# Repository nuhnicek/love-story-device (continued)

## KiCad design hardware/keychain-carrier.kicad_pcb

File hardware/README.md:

# Hardware — GSM touch keychain

Two boards per keychain:

1. **Carrier** (this folder): a 2-layer, **0.8 mm** board with the **same 25.2 × 23.0 mm
   outline as the red SIM800L mini module**. The module sits on top and is soldered
   straight through its own 12 holes. All electronics are on the **bottom** side, facing
   the LiPo cell. The separate TP4056 board is gone: USB-C and a TP4054 charger chip are
   on the carrier.
2. **Heart LED board**: hand-built on a **universal board** (11 × 9 holes) with **10 × 3 mm
   LEDs** in a heart, one resistor each, and the coin motor in the middle. The LED domes
   stick out through holes in the case lid. Wired to the carrier's `HEART +/-` pads. See
   [Heart LED board](#heart-led-board).

Cost: see [COST.md](COST.md). ≈ 1 450–2 900 Kč for the self-assembled pair incl. 1NCE SIMs
for 10 years. Firmware: [`../firmware`](../firmware). Relay server: [`../server`](../server).

| File | What |
|---|---|
| `keychain-carrier.kicad_sch` | **Schematic** (KiCad 10). PDF/SVG: `fab/schematic.pdf`, `fab/schematic.svg` |
| `keychain-carrier.kicad_pcb` / `.kicad_pro` / `.kicad_dru` | KiCad 10 board, project, custom DRC rule |
| `keychain.kicad_sym`, `keychain.pretty/`, `sym-lib-table`, `fp-lib-table` | Project library: SIM800L symbol + footprint, VBAT power symbol, wire pads |
| `netlist.txt` | Netlist extracted from the board copper |
| `BOM.md` | Full parts list (carrier + perfboard heart + off-board) |
| `COST.md` | Manufacturing and running-cost estimate |
| `fab/keychain-carrier-gerbers.zip` | Gerbers + Excellon drill, ready to upload |
| `fab/keychain-carrier-bom-jlcpcb.csv`, `fab/keychain-carrier-pos-bottom.csv` | JLCPCB assembly files (bottom side) |
| `fab/assembly-bottom.pdf` | Assembly drawing with designators (bottom, mirrored) |
| `fab/keychain-carrier.step` | 3D model for the enclosure design |
| `scripts/` | Generator: `make_all.sh <freerouting.jar>` rebuilds everything |

Checks (all run by `make_all.sh`):
- **ERC**: 0 violations
- **DRC**: 0 errors, 0 unconnected (one cosmetic silk note)
- **Schematic ↔ PCB parity**: 0 issues. Every footprint is linked to its symbol, and the
  pad nets and fields come from the schematic netlist.

## Pin map (ATtiny85, RESET kept for ISP)

| ATtiny85 pin | Port | Net | Goes to |
|---|---|---|---|
| 1 | PB5 / RESET | RESET | 10 k pull-up to VBAT, ISP pad TP1 |
| 2 | PB3 | RST_DRV | 1 kΩ → SIM800L RST (pin 3). Open-drain hard reset of a hung modem; never driven high |
| 3 | PB4 | DRV | 100 Ω → AO3400A gate (100 k pull-down). Motor **and** heart LEDs |
| 4 | GND | GND | |
| 5 | PB0 / MOSI | MCU_RX | 1 k ← SIM800L TXD (SoftwareSerial RX). ISP TP2 |
| 6 | PB1 / MISO | MCU_TX | 47 k / 100 k divider → SIM800L RXD (≈2.86 V at 4.2 V). ISP TP3 |
| 7 | PB2 / SCK | BTN | Side button to GND (internal pull-up), PCINT2. ISP TP4 |
| 8 | VCC | VBAT | 100 nF |

Five I/O pins can't cover TX, RX, RING, button, motor, LEDs and DTR separately. So:
- **Heart LEDs and motor share PB4.** The heart board hangs in parallel with the motor on
  the MOSFET drain (pads HT1/HT2), so the heart glows exactly with the vibration. Q1 is an
  **AO3400A** (~50 mΩ) instead of the 2N7002 (2–5 Ω). With motor + 14 LEDs (~150 mA) a
  2N7002 would drop 0.3–0.7 V and visibly dim the pink LEDs. Same SOT-23 footprint and pinout.
- **DTR and RING are not used** (1NCE data design). The modem sleeps by itself
  (`AT+CSCLK=2`). Incoming TCP data is held in the modem (`AT+CIPRXGET=1`), and its URC on
  the UART line wakes the ATtiny85. That frees PB3 to hard-reset the modem.
- **SoftwareSerial owns the only PCINT vector** on the ATtiny85. The button shares it
  (`PCMSK |= _BV(PCINT2)`); SoftwareSerial's ISR ignores changes on pins other than its RX.
- **Charger: TP4054** (pin-compatible with the MCP73831; 4.7 kΩ on PROG = 213 mA). It's a
  standalone linear Li-ion charger with thermal regulation, the same circuit class as the
  TP4056, at about a tenth of the MCP73831's price. A transistor-only charger wouldn't be
  cheaper and would be much less safe.
- Firmware: `../firmware`. Relay server: `../server`.

## Schematic (ASCII quick view; the real one is `keychain-carrier.kicad_sch`)

```
 USB-C (power only)                TP4054 (U2)                  LiPo 3.7 V
 VBUS ──┬──────────────────────── 4 VDD     VBAT 3 ──┬───────────── BT1 (+)
        C3 4.7u                     5 PROG─R10 4k7─GND │            BT2 (-) ── GND
 CC1 ── R8 5k1 ── GND               1 CHRG (n.c.)    C4 4.7u
 CC2 ── R9 5k1 ── GND               2 VSS ── GND       │
                                                       │ VBAT
        ┌──────────────────────────────────────────────┼───────────────────┐
        │                                              │                   │
  SIM800L M1 (top side)              C2 470u tant ═╪═ C5 10u       ATtiny85 U1
   2 VCC ──────────────────────────────────────────────┤             8 VCC ──┤ C1 100n
   6 GND ── GND                                         R6 10k ─── 1 RESET ── TP1
   5 TXD ── R1 1k ──────────────────────────────────────────────── 5 PB0 ── TP2
   4 RXD ──┬── R2 47k ──────────────────────────────────────────── 6 PB1 ── TP3
           R3 100k ── GND                                          7 PB2 ── TP4 ── SW1 ── GND
   3 RST ── R7 1k ──────────────────────────────────────────────── 2 PB3 (open drain)
   1 NET, 7–12 (SPK/MIC/DTR/RING): not connected                   3 PB4 ── R4 100R ──┐
                                                                    4 GND             │
  VBAT ─┬─ MT1 (motor +)    VBAT ─ HT1 ═ heart board ═ HT2 ─┐             R5 100k ─┤ G
        │   [0820 motor]                                     │                GND   Q1 AO3400A
        D1 (K)─┘ MT2 (motor −) ──────────────────────────────┴───────────────── D   S ── GND
```

## Silkscreen labels

Every connection point is labelled (0.8 mm text, about the smallest that prints legibly):

- **Bottom:** `BAT` `+`/`-` (battery), `MOT` (motor pads, polarity doesn't matter for a
  coin motor), `HEART` `+`/`-` (heart board wires), and `ISP` with `RST`, `MOSI`, `MISO`,
  `SCK`, `VCC`, `GND` next to each programming pad.
- **Top:** the name of every SIM800L hole (`NET VCC RST RXD TXD GND` / `RING DTR MIC± SPK±`)
  so the module can't go on the wrong way round, plus `TOUCH-GSM v1 / SIM800L SIDE`.

Part references (R1, U1…) are only on the assembly drawing (`fab/assembly-bottom.pdf`);
there's no room for them on the copper side.

## Heart LED board

- **Board:** a universal board (2.54 mm, single-sided pads) cut to **11 × 9 holes =
  27.9 × 22.9 mm**.
- **LEDs:** 10 × 3 mm LEDs stand in a heart, each with its two legs in vertically adjacent
  holes.
- **Resistors:** one 1/8 W resistor per LED, lying flat next to its LED: 470 Ω for
  pink/white/blue LEDs (Vf ≈ 3 V), or 1 kΩ for red. That's ~1.5–3 mA per LED, ≤ 30 mA total.
  Use LEDs from one bag so they match.
- **Motor:** the 0820 coin motor sticks onto the free middle of the heart, on the component
  side.
- **Wiring** (underside, insulated thin wire): bridge each LED's anode to the resistor end
  next to it. One wire joins all the far resistor ends (`+`, to the carrier's `HEART +` =
  HT1). Another joins all the LED cathodes (`-`, to `HEART -` = HT2).
- **Hole-by-hole list:** `enclosure/out/heart_perfboard.txt`. The layout comes from
  `enclosure/heart_perfboard.py`, which also writes the LED and post positions the case lid
  uses, so the lid holes always match the drawing.
- **LED height:** the LEDs must sit **flat on the board** (flange down). The lid is
  designed for LEDs 5.3 mm tall from flange to dome top. If yours differ, set `led_h` in
  `enclosure/keychain_case.scad` and rebuild.

## Battery connection

There's no plug-in connector. The LiPo leads solder straight onto two 1.5 × 1.5 mm pads
(2 mm apart) in the **middle of the bottom side**, just above the USB-C and below the
ATtiny85. Looking at the bottom with the USB-C toward you, **BT1 "+" (red) is on the right
and BT2 "−" (black) is on the left**. Both are marked on the silkscreen. There is **no
reverse-polarity protection**, so check twice before soldering. A JST-SH 1.0 mm 2-pin
socket (~2.9 mm tall) could replace the pads if you want a pluggable battery.

## Assembly order (important)

1. **Flash the ATtiny85 before the SIM800L goes on.** The ISP pads (TP1–TP6, bottom-left)
   share the VBAT rail with the SIM800L, which has an **absolute maximum of 4.4 V**. A 5 V
   Arduino-as-ISP powering VCC (or driving 5 V signals into a 4 V target) will hurt the
   module. Use either (a) program the bare carrier, or (b) a 3.3 V programmer with the
   battery connected and the programmer's VCC wire left off.
2. Solder all bottom-side SMD parts (or order JLCPCB assembly with the CSV/POS files).
   The KiCad footprint for the USB-C is GCT USB4125; cheap "TYPE-C 6P" clones share
   the land, but check the drawing.
3. Insert the micro-SIM into the module, then place the module on the carrier top. The
   SIM holder rests on the solder-masked carrier, giving ~1.5 mm spacing. Push 12 pins
   (from a header strip, plastic removed) through both boards, solder both sides, and cut
   flush on the bottom.
4. Wire the battery to BT1/BT2 and the motor to MT1/MT2 (≈20 mm leads, the motor sticks
   to the enclosure wall).
5. Wire the heart perfboard: its `+` wire to carrier `HEART +` (HT1) and its `-` wire to
   `HEART -` (HT2), ~25 mm each. It sits on top of the SIM800L (tape in between), LEDs up.

## Things to check before ordering

- **SIM800L hole geometry.** Taken from a community footprint: rows **21.87 mm** apart,
  2.54 mm pitch, right row (RING…SPK−) offset one pitch lower than the left row
  (NET…GND), outline 25.2 × 23 mm. Measure your Hadex M374C with calipers and change
  `ROW_DX` / `RIGHT_ROW_DY` / `BW` / `BH` in `scripts/build_pcb.py` if needed, then rerun
  `make_all.sh`.
- **Tantalum C2.** 4.2 V on a 6.3 V *MnO₂* tantalum breaks the usual 50 % derating, and
  those fail short on inrush (e.g. when the battery is first connected). Use a **polymer**
  tantalum (Kemet T520D477M006…, listed in the BOM) or a 10 V part.
- **Battery must have its own protection PCM.** The carrier has no over-discharge cut-off.
- **2G availability in Czechia.** Czech operators switched off 3G but still run 2G. Check
  that your operator's 2G will stay on for as long as you want the keychains to work.

## Height budget (for the enclosure)

| Layer | mm |
|---|---|
| SIM800L module incl. shield | ~3.0 |
| SIM holder gap (module underside) | ~1.5 |
| Carrier PCB | 0.8 |
| Tallest bottom part (USB-C 3.2 / tantalum 3.1) | 3.2 |
| LiPo | 4.0 |
| Heart perfboard: wiring underneath 1.3 + board 1.6 + space up to the lid 2.6 | ~5.5 |
| **Total inside** | **~18.4** (case 20.8 mm + 1.5 mm LED domes) |

The 11 mm target can't be reached with a Case-D tantalum, a top-mount USB-C and a 4 mm
cell all stacked. To get close: use a 3 mm cell (e.g. 302025, ~150 mAh) and pocket the
battery around the USB-C/tantalum.

## Design flow / editing

`gen_schematic.py` → `.kicad_sch` (source of truth)
→ `build_pcb.py` places footprints, then **imports nets and fields from the schematic
netlist** (and fails if they disagree with its own pin map)
→ `autoroute.py` (Freerouting, retried with varied pass budgets; fails if anything stays
unrouted) → GND pours (carrier) → DRC + parity + ERC → fab outputs.
Shared code: `schlib.py` (schematic writer), `pcblib.py` (pcbnew helpers), `sexpr.py`.

To change the circuit, edit the scripts and rerun `make_all.sh`. Regenerating
overwrites the `.kicad_sch` / `.kicad_pcb`, so if you'd rather edit by hand in KiCad
from now on, stop running the scripts and use KiCad's *Update PCB from Schematic*. The
footprint↔symbol links are already in place.

## Regenerate

```sh
# needs KiCad 10 and Java 25+ for Freerouting 2.5.0
curl -LO https://github.com/freerouting/freerouting/releases/download/v2.5.0/freerouting-2.5.0.jar
# sha256 f6f51bb02245e8e717f9359bd260cc9c5c0b1bc0acc8b7cb2cd5b8ffeb5de3c7
hardware/scripts/make_all.sh ./freerouting-2.5.0.jar
```

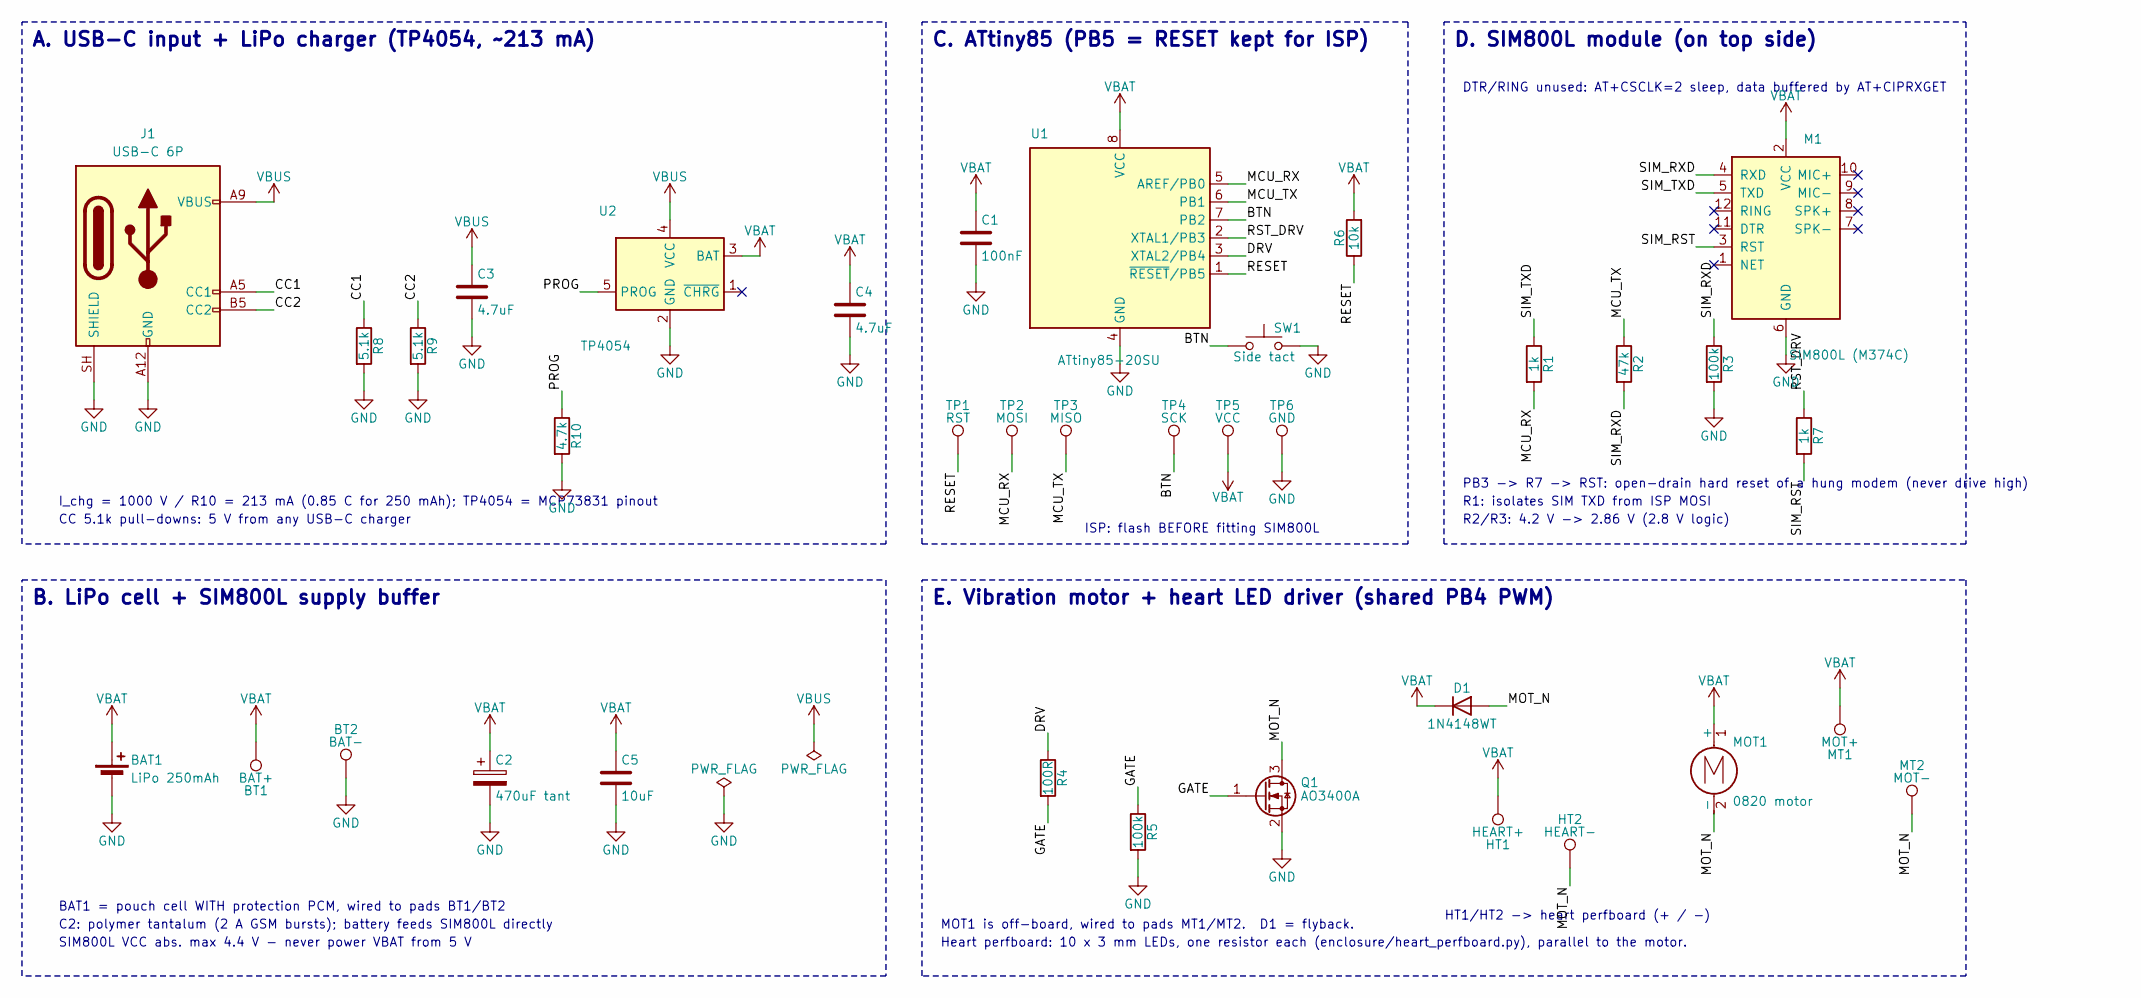
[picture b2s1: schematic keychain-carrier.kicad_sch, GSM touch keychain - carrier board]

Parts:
BAT1: LiPo 250mAh
BT1: BAT+; WirePad_1.5mm
BT2: BAT-; WirePad_1.5mm
C1: 100nF; C_0402_1005Metric
C2: 470uF tant; CP_EIA-7343-31_Kemet-D
C3, C4: 4.7uF; C_0402_1005Metric
C5: 10uF; C_0603_1608Metric; LCSC C19702
D1: 1N4148WT; D_SOD-523
HT1: HEART+; WirePad_1.0mm
HT2: HEART-; WirePad_1.0mm
J1: USB-C 6P; USB_C_Receptacle_GCT_USB4125-xx-x_6P_TopMnt_Horizontal
M1: SIM800L (M374C); SIM800L_Red_Mini_25.2x23
MOT1: 0820 motor
MT1: MOT+; WirePad_1.0mm
MT2: MOT-; WirePad_1.0mm
Q1: AO3400A; SOT-23
R1, R7: 1k; R_0402_1005Metric; LCSC C11702
R2: 47k; R_0402_1005Metric; LCSC C25792
R3, R5: 100k; R_0402_1005Metric; LCSC C25741
R4: 100R; R_0402_1005Metric; LCSC C25076
R6: 10k; R_0402_1005Metric; LCSC C25744
R8, R9: 5.1k; R_0402_1005Metric; LCSC C25905
R10: 4.7k; R_0402_1005Metric; LCSC C25900
SW1: Side tact; SW_Push_1P1T-MP_NO_Horizontal_Alps_SKRTLAE010
TP1: RST; WirePad_0.9mm
TP2: MOSI; WirePad_0.9mm
TP3: MISO; WirePad_0.9mm
TP4: SCK; WirePad_0.9mm
TP5: VCC; WirePad_0.9mm
TP6: GND; WirePad_0.9mm
U1: ATtiny85-20SU; SOIC-8_3.9x4.9mm_P1.27mm
U2: TP4054; SOT-23-5

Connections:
/BTN: SW1.1, TP4.1, U1.7 (PB2)
/CC1: J1.A5 (CC1), R8.1
/CC2: J1.B5 (CC2), R9.1
/DRV: R4.1, U1.3 (XTAL2/PB4)
/GATE: Q1.1 (G), R4.2, R5.1
/MCU_RX: R1.2, TP2.1, U1.5 (AREF/PB0)
/MCU_TX: R2.1, TP3.1, U1.6 (PB1)
/MOT_N: D1.2 (A), HT2.1, MOT1.2 (-), MT2.1, Q1.3 (D)
/PROG: R10.1, U2.5 (PROG)
/RESET: R6.1, TP1.1, U1.1 (~RESET/PB5)
/RST_DRV: R7.1, U1.2 (XTAL1/PB3)
/SIM_RST: M1.3 (RST), R7.2
/SIM_RXD: M1.4 (RXD), R2.2, R3.1
/SIM_TXD: M1.5 (TXD), R1.1
GND: BAT1.2 (-), BT2.1, C1.2, C2.2, C3.2, C4.2, C5.2, J1.A12 (GND), J1.B12 (GND), J1.SH (SHIELD), M1.6 (GND), Q1.2 (S), R3.2, R5.2, R8.2, R9.2, R10.2, SW1.2, TP6.1, U1.4 (GND), U2.2 (GND)
VBAT: BAT1.1 (+), BT1.1, C1.1, C2.1, C4.1, C5.1, D1.1 (K), HT1.1, M1.2 (VCC), MOT1.1 (+), MT1.1, R6.2, TP5.1, U1.8 (VCC), U2.3 (BAT)
VBUS: C3.1, J1.A9 (VBUS), J1.B9 (VBUS), U2.4 (VCC)

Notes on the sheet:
A. USB-C input + LiPo charger (TP4054, ~213 mA)
I_chg = 1000 V / R10 = 213 mA (0.85 C for 250 mAh); TP4054 = MCP73831 pinout
CC 5.1k pull-downs: 5 V from any USB-C charger
B. LiPo cell + SIM800L supply buffer
BAT1 = pouch cell WITH protection PCM, wired to pads BT1/BT2
C2: polymer tantalum (2 A GSM bursts); battery feeds SIM800L directly
SIM800L VCC abs. max 4.4 V - never power VBAT from 5 V
C. ATtiny85 (PB5 = RESET kept for ISP)
ISP: flash BEFORE fitting SIM800L
D. SIM800L module (on top side)
R1: isolates SIM TXD from ISP MOSI
R2/R3: 4.2 V -> 2.86 V (2.8 V logic)
DTR/RING unused: AT+CSCLK=2 sleep, data buffered by AT+CIPRXGET
PB3 -> R7 -> RST: open-drain hard reset of a hung modem (never drive high)
E. Vibration motor + heart LED driver (shared PB4 PWM)
HT1/HT2 -> heart perfboard (+ / -)
MOT1 is off-board, wired to pads MT1/MT2. D1 = flyback.
Heart perfboard: 10 x 3 mm LEDs, one resistor each (enclosure/heart_perfboard.py), parallel to the motor.

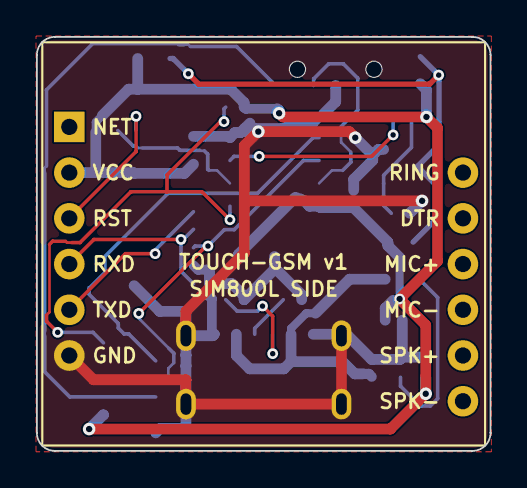
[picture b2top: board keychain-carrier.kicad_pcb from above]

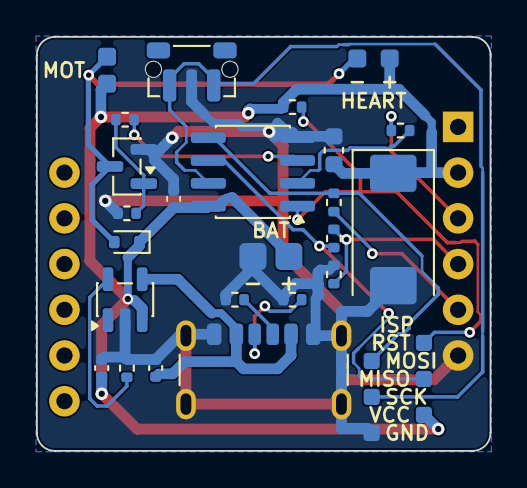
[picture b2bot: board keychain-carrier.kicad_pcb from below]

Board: 2 copper layers, 25.2 x 23.0 mm, 34 parts (33 on the bottom side), 17 nets.

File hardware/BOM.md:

# Parts list — GSM touch keychain (per keychain; build x2)

Generated by `hardware/scripts/bom.py` from the KiCad boards. LCSC numbers are filled
only where checked; otherwise search the MPN.

## Carrier board (25.2 x 23 mm, parts on the bottom side)

| Ref | Qty | Value | Description | Suggested MPN | Footprint | LCSC |
|---|---|---|---|---|---|---|
| C1 | 1 | 100nF | MLCC 100 nF 16 V X7R 0402 | Samsung CL05B104KO5NNNC | C_0402_1005Metric |  |
| C2 | 1 | 470uF tant | Polymer tantalum 470 uF 6.3 V, EIA-7343-31 (Case D), low ESR | Kemet T520D477M006ATE015 | CP_EIA-7343-31_Kemet-D |  |
| C3, C4 | 2 | 4.7uF | MLCC 4.7 uF 10 V X5R 0402 | Samsung CL05A475KP5NRNC | C_0402_1005Metric |  |
| C5 | 1 | 10uF | MLCC 10 uF 10 V X5R 0603 | Samsung CL10A106KP8NNNC | C_0603_1608Metric | C19702 |
| D1 | 1 | 1N4148WT | Switching diode, SOD-523 (motor flyback) | 1N4148WT | D_SOD-523 |  |
| J1 | 1 | USB-C 6P | USB-C receptacle, power-only 6-pin, top-mount | GCT USB4125-GF-A (or TYPE-C 6P clone, same land) | USB_C_Receptacle_GCT_USB4125-xx-x_6P_TopMnt_Horizontal |  |
| Q1 | 1 | AO3400A | N-MOSFET 30 V 5.7 A, ~50 mOhm, SOT-23 (motor + heart driver) | AOS AO3400A | SOT-23 |  |
| R1, R7 | 2 | 1k | Resistor 1 k 1% 0402 (SIM TXD -> PB0 ISP isolation; PB3 -> SIM RST) | UNI-ROYAL 0402WGF1001TCE | R_0402_1005Metric | C11702 |
| R2 | 1 | 47k | Resistor 47 k 1% 0402 (TX divider top) | UNI-ROYAL 0402WGF4702TCE | R_0402_1005Metric | C25792 |
| R3, R5 | 2 | 100k | Resistor 100 k 1% 0402 (TX divider bottom / gate pull-down) | UNI-ROYAL 0402WGF1003TCE | R_0402_1005Metric | C25741 |
| R4 | 1 | 100R | Resistor 100 R 1% 0402 (gate) | UNI-ROYAL 0402WGF1000TCE | R_0402_1005Metric | C25076 |
| R6 | 1 | 10k | Resistor 10 k 1% 0402 (RESET pull-up) | UNI-ROYAL 0402WGF1002TCE | R_0402_1005Metric | C25744 |
| R8, R9 | 2 | 5.1k | Resistor 5.1 k 1% 0402 (USB-C CC pull-down) | UNI-ROYAL 0402WGF5101TCE | R_0402_1005Metric | C25905 |
| R10 | 1 | 4.7k | Resistor 4.7 k 1% 0402 (charge current ~213 mA) | UNI-ROYAL 0402WGF4701TCE | R_0402_1005Metric | C25900 |
| SW1 | 1 | Side tact | Side-push tactile switch 3.5 x 2.9 mm, SMD | Alps SKRTLAE010 | SW_Push_1P1T-MP_NO_Horizontal_Alps_SKRTLAE010 |  |
| U1 | 1 | ATtiny85-20SU | MCU, 8 KB flash, SOIC-8 (150 mil) | Microchip ATTINY85-20SU | SOIC-8_3.9x4.9mm_P1.27mm |  |
| U2 | 1 | TP4054 | Li-Ion/LiPo linear charger 4.20 V, SOT-23-5 (MCP73831 pinout) | TP4054 (NanJing Top Power or equivalent) | SOT-23-5 |  |

21 placed parts, 17 unique lines.

## Off-board / mechanical

| Ref | Qty | Item | Example |
|---|---|---|---|
| M1 | 1 | SIM800L red mini GSM module (Hadex M374C), soldered on carrier TOP through its 12 holes | SIM800L mini |
| — | 12 | Header pins / 0.6 mm tinned copper wire, cut flush (module-to-carrier) | 2.54 mm male header strip, pins pulled |
| BT1/BT2 | 1 | LiPo pouch 3.7 V 250–300 mAh, max ~25 x 20 x 4 mm, WITH protection PCM | e.g. 402025 / 502025 |
| MT1/MT2 | 1 | Coin vibration motor 0820 (Ø8 x 2 mm, 3 V), adhesive back | 0820 coin motor |
| HEART | 1 | Universal board (perfboard, 2.54 mm, single-sided pads), cut to 11 x 9 holes = 27.9 x 22.9 mm | any FR-4 dot board |
| HEART | 10 | 3 mm through-hole LED, diffused, all from one bag (pink/white/blue Vf ~3 V, or red ~2 V) | 3 mm LED |
| HEART | 10 | Resistor 1/8 W (mini, ~1.8 x 3.3 mm body), 470 R for pink/white/blue LEDs or 1 k for red | 1/8 W metal film |
| HEART | 1 | Insulated thin wire for the +/- buses and to carrier HT1/HT2 (0.1-0.2 mm enamelled / Kynar) | — |
| — | 1 | Antenna: SIM800L spring/helical antenna (supplied) or u.FL FPC antenna | — |
| — | 1 | Micro-SIM card with 2G (T-Mobile CZ / Vodafone CZ / O2 CZ), PIN disabled | — |
| TP1–TP6 | 1 | 0.1 mm enamelled wire or pogo clip for ISP (RST/MOSI/MISO/SCK/VCC/GND) | — |

## PCBs

- **Carrier**: 2-layer FR-4, 0.8 mm, 1 oz, 25.2 x 23.0 mm, min track/space 0.127/0.127 mm, via 0.3/0.6 mm. Gerbers: `fab/keychain-carrier-gerbers.zip`.
- **Heart**: hand-built on a universal board, layout in `enclosure/out/heart_perfboard.png` (generated by `enclosure/heart_perfboard.py`).

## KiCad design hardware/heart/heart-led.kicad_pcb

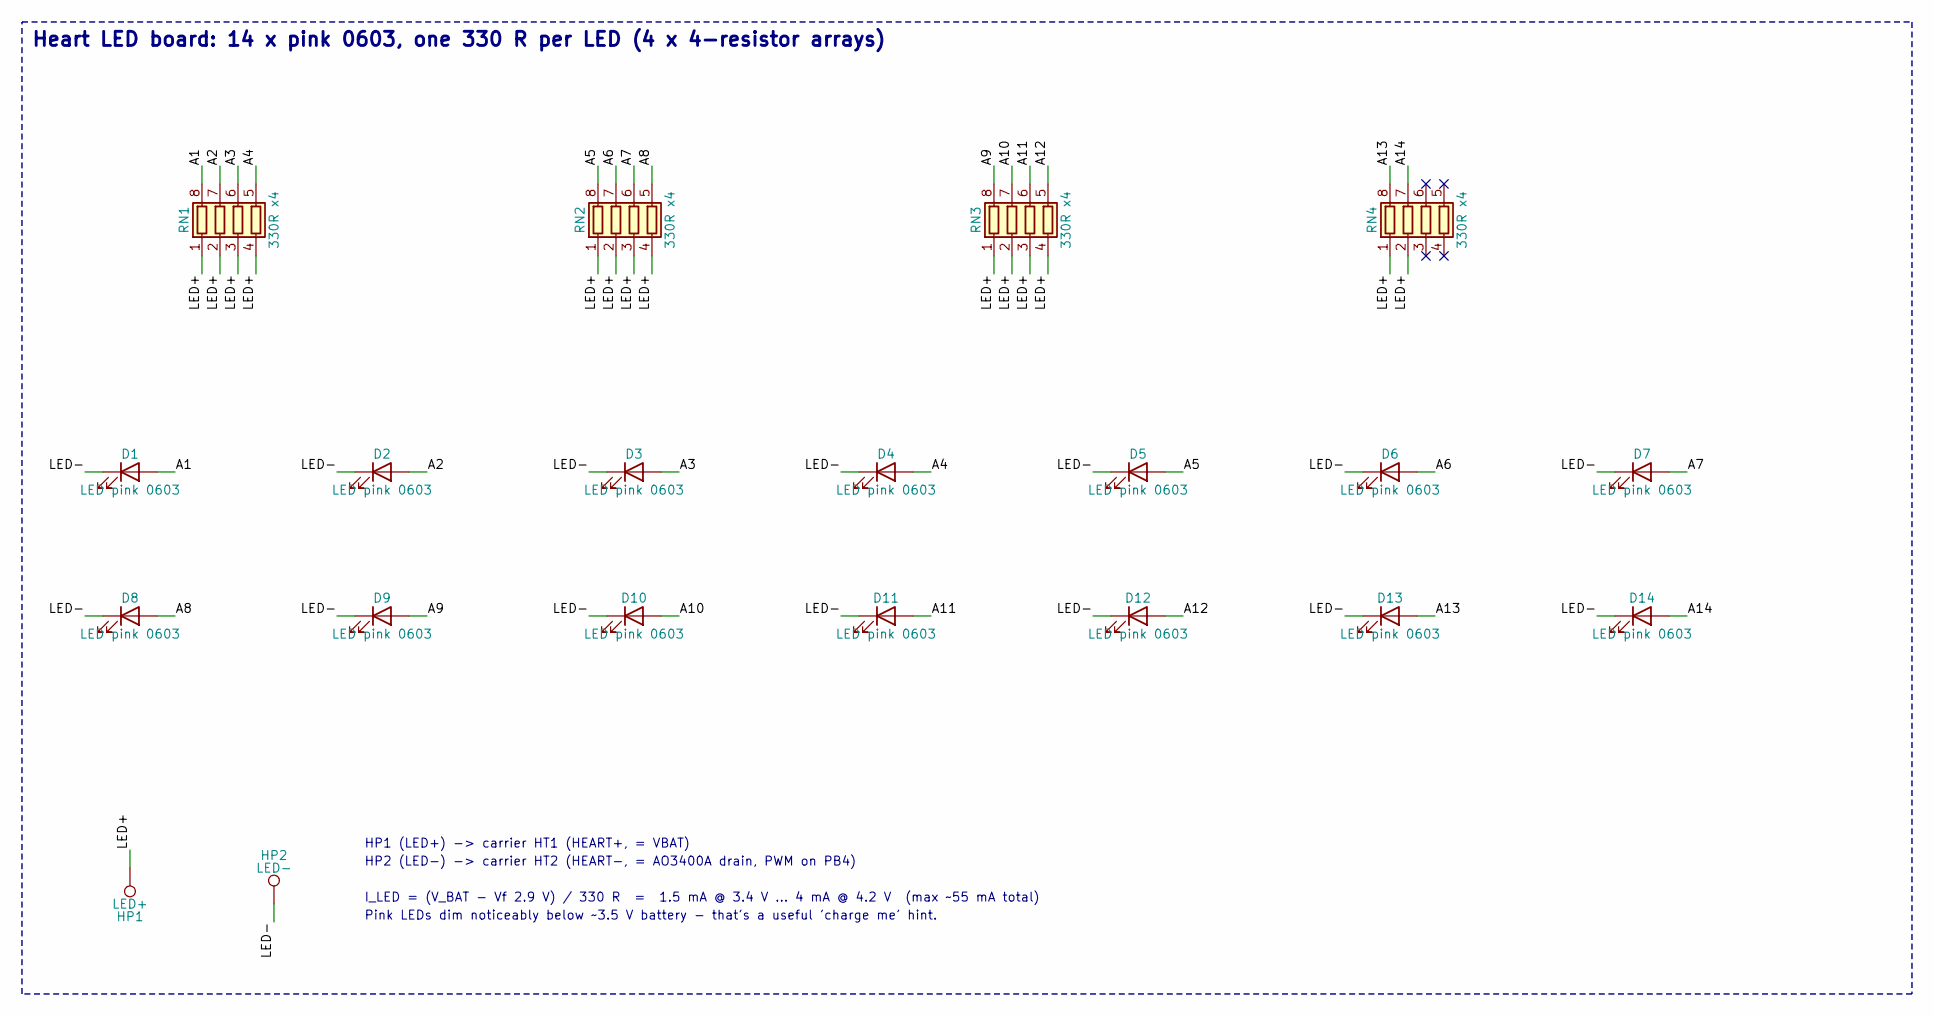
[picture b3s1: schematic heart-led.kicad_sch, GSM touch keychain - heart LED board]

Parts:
D1, D2, D3, D4, D5, D6, D7, D8, D9, D10, D11, D12, D13, D14: LED pink 0603; LED_0603_1608Metric
HP1: LED+; WirePad_1.0mm
HP2: LED-; WirePad_1.0mm
RN1, RN2, RN3, RN4: 330R x4; R_Array_Convex_4x0402

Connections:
/A1: D1.2 (A), RN1.8 (R1.2)
/A2: D2.2 (A), RN1.7 (R2.2)
/A3: D3.2 (A), RN1.6 (R3.2)
/A4: D4.2 (A), RN1.5 (R4.2)
/A5: D5.2 (A), RN2.8 (R1.2)
/A6: D6.2 (A), RN2.7 (R2.2)
/A7: D7.2 (A), RN2.6 (R3.2)
/A8: D8.2 (A), RN2.5 (R4.2)
/A9: D9.2 (A), RN3.8 (R1.2)
/A10: D10.2 (A), RN3.7 (R2.2)
/A11: D11.2 (A), RN3.6 (R3.2)
/A12: D12.2 (A), RN3.5 (R4.2)
/A13: D13.2 (A), RN4.8 (R1.2)
/A14: D14.2 (A), RN4.7 (R2.2)
/LED+: HP1.1, RN1.1 (R1.1), RN1.2 (R2.1), RN1.3 (R3.1), RN1.4 (R4.1), RN2.1 (R1.1), RN2.2 (R2.1), RN2.3 (R3.1), RN2.4 (R4.1), RN3.1 (R1.1), RN3.2 (R2.1), RN3.3 (R3.1), RN3.4 (R4.1), RN4.1 (R1.1), RN4.2 (R2.1)
/LED-: D1.1 (K), D2.1 (K), D3.1 (K), D4.1 (K), D5.1 (K), D6.1 (K), D7.1 (K), D8.1 (K), D9.1 (K), D10.1 (K), D11.1 (K), D12.1 (K), D13.1 (K), D14.1 (K), HP2.1

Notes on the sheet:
Heart LED board: 14 x pink 0603, one 330 R per LED (4 x 4-resistor arrays)
HP1 (LED+) -> carrier HT1 (HEART+, = VBAT)
HP2 (LED-) -> carrier HT2 (HEART-, = AO3400A drain, PWM on PB4)
I_LED = (V_BAT - Vf 2.9 V) / 330 R = 1.5 mA @ 3.4 V ... 4 mA @ 4.2 V (max ~55 mA total)
Pink LEDs dim noticeably below ~3.5 V battery - that's a useful 'charge me' hint.

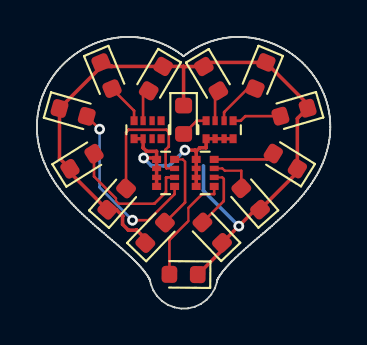
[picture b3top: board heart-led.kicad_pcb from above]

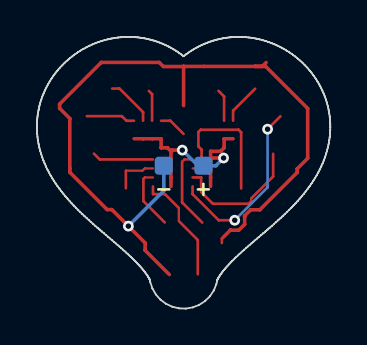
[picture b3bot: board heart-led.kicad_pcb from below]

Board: 2 copper layers, 16.3 x 15.1 mm, 20 parts (2 on the bottom side), 16 nets.

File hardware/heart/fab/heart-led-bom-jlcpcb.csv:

Comment,Designator,Footprint,LCSC Part #
LED pink 0603,"D1,D2,D3,D4,D5,D6,D7,D8,D9,D10,D11,D12,D13,D14",LED_0603_1608Metric,
330R x4,"RN1,RN2,RN3,RN4",R_Array_Convex_4x0402,

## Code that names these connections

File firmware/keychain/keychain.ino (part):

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 * while a keychain is out of coverage.
 *
 * Pins (carrier board netlist):
 *   PB0  MCU_RX  <- 1k <- SIM800L TXD     (SoftwareSerial RX, also ISP MOSI)
 *   PB1  MCU_TX  -> 47k/100k -> SIM RXD   (SoftwareSerial TX, also ISP MISO)
 *   PB2  BTN     side button to GND       (internal pull-up, also ISP SCK)
 *   PB3  RST_DRV -> 1k -> SIM800L RST     (open drain: only ever driven LOW)
 *   PB4  DRV     -> AO3400A gate          (PWM: motor + heart board together)
 *   PB5  RESET                            (kept for ISP)
 *
 * Power: the ATtiny85 sleeps in power-down. It wakes on the button, on any UART
 * activity from the modem (incoming data is held in the modem by AT+CIPRXGET=1, so
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
#define PIN_RX 0
#define PIN_TX 1
#define PIN_BTN 2
#define PIN_SRST 3
#define PIN_DRV 4

#define STR_(x) #x
#define STR(x) STR_(x)
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}

/* ------------------------------------------------------------------ motor + heart */
static void driveOn() { analogWrite(PIN_DRV, DRIVE_PWM); }
static void driveOff() { analogWrite(PIN_DRV, 0); digitalWrite(PIN_DRV, LOW); }

static void playBuzz() { /* 1.5 s: three pulses */
  for (uint8_t i = 0; i < 3; i++) { driveOn(); delayPet(300); driveOff(); delayPet(200); }
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  uint32_t t0 = millis();
  for (;;) {
    petDog();
    if (digitalRead(PIN_BTN) != level) {
      delay(DEBOUNCE_MS);
      if (digitalRead(PIN_BTN) != level) break;
    }
    if (level == HIGH && millis() - t0 >= maxMs) return maxMs;
  }
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  sleep_cpu();
  sleep_disable();
  /* woken by a pin change that wasn't the button -> the modem has something for us */
  if (wdtTicks == before && digitalRead(PIN_BTN) == HIGH) rxActivity = 1;
}

void setup() {
  stackPaint();
  pinMode(PIN_BTN, INPUT_PULLUP);
  digitalWrite(PIN_SRST, LOW);
  pinMode(PIN_SRST, INPUT);
  pinMode(PIN_DRV, OUTPUT);
  driveOff();
  ACSR |= _BV(ACD);       /* analog comparator off */
  ADCSRA &= ~_BV(ADEN);   /* ADC off */
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
void loop() {
  petDog();
  if (digitalRead(PIN_BTN) == LOW) handleGesture();

  if (connected && (rxActivity || dataPending)) {
    rxActivity = 0;
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
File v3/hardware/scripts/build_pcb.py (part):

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      pads={"1": "SIM_RST", "2": "SIM_CLK", "4": "SIM_IO", "5": "SIM_1V8", "3": "GND", "8": "GND"})
place(C06, "C13", "100nF", 107.2, 117.4, 180, bottom=True, pads={"1": "SIM_1V8", "2": "GND"})

# --- top band: VDD_GPIO decoupling, gate resistor
C("C10", "100nF", 114.0, 101.5, "+3V0", "GND", rot=180)      # +3V0 pad right above pin 65
C("C11", "4.7uF", 124.1, 104.5, "+3V0", "GND", rot=90)     # beside the +3V0 lane (the heart tip sits above the SiP now)
R("R7", "100R", 117.2, 101.5, "DRV", "GATE")
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      pads={"1": "LTE_ANT", "2": "GND"})

# --- DEC0
C("C9", "4.7uF", UX - 3.25, 116.0, "DEC0", "GND", rot=270)  # right below pin 24

# --- power band: ferrite, VBAT caps, charger, CC resistors
place("Inductor_SMD:L_0805_2012Metric", "FB1", "22R@100MHz 6A", 100.4, 115.65, 0,
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            "23": "CP_DTR"})
place("Package_TO_SOT_SMD:SOT-23", "Q2", "DTC114E", 110.4, 123.3, 180,     # pins 1/2 face U5: E-RTS top, B-DTR bottom
      pads={"1": "CP_DTR", "2": "CP_RTS", "3": "nRESET"})
# right of U5, in pin order: RST pull-up, VBUS-sense divider, VREGIN cap; USB_DET divider
R("R11", "10k", 119.4, 122.9, "V3U", "CP_RST", fp=R04)
R("R10", "47.5k", 119.4, 124.0, "USB_VSNS", "GND", fp=R04)
R("R9", "22.1k", 119.4, 125.1, "VBUS", "USB_VSNS", fp=R04)
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      pads={"1": "VBAT", "2": "GND", "3": "LED_EN", "6": "VLED"})
C("C19", "1uF", U6X - 3.1, U6Y - 0.95, "VBAT", "GND", fp=C04, rot=180)   # VBAT pad towards pin 1
R("R17", "100k", U6X + 1.5, U6Y + 2.7, "LED_EN", "GND", fp=R04)
C("C20", "10uF", U6X + 3.9, U6Y - 0.95, "VLED", "GND")                  # right at U6's output pin
place("Package_TO_SOT_SMD:SOT-23-5", "U7", "SN74LV1T34DBV", U7X, U7Y, 0,
      pads={"2": "LED_DATA3V", "3": "GND", "4": "LED_DIN", "5": "VLED"})
C("C21", "100nF", U7X + 3.3, U7Y - 0.95, "VLED", "GND", fp=C04)
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    via(vx, vy, n)
    path([u4[pin], V(vx, vy)], n, w=0.15)
    bpath([(vx, vy), (X(j3[cont]), vy), (X(j3[cont]), Y(j3[cont]))], n)
# VCC (SIM_1V8): via below pin 5, bottom run left and up to contact 1, C13 on the way
vy = Y(u4["5"]) + 0.75
via(xp, vy, VCCN)
path([u4["5"], V(xp, vy)], VCCN, w=0.15)
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bpath([(xp, vy), (108.9, vy), (108.9, Y(j3["1"]))], VCCN)
bpath([(108.9, Y(c13)), (X(c13), Y(c13))], VCCN)

# SIM_1V8 from the SiP: pin 19 -> via (left of the SiP corner) -> bottom run into the VCC line
p19 = pad_pos("U1", "19")
via(104.9, 113.35, VCCN)
path([p19, V(105.5, Y(p19)), V(104.9, 113.35)], VCCN, w=0.15)
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r4v = pad_pos("R4", "1")
path([r4v, V(99.4, Y(r4v)), V(99.4, 110.0), V(X(pad_pos("C5", "1")), 110.0)], net_of("U1", "14"), w=0.2)

# BTN: SiP pin 49 (P0.30) -> via clear of the SIM holder's shield pad -> bottom layer
# down the right side -> via in SW1's pad
b49, sw = pad_pos("U1", "49"), pad_pos("SW1", "1")
BTNN = net_of("U1", "49")
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u6o, c20 = pad_pos("U6", "6"), pad_pos("C20", "1")
path([u6o, c20], net_of("U6", "6"), w=0.3)

# SIM_CLK: SiP pin 18 -> via left of the SiP (above the SIM-VCC via) -> inner layer 3
# -> the CLK via next to U4
p18 = pad_pos("U1", "18")
CLKN = net_of("U1", "18")
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via(104.6, Y(p18) + 0.25, CLKN)
ipath([(104.6, Y(p18) + 0.25), (105.9, Y(p18) + 0.25), (109.45, Y(p18) + 3.8), (109.45, 117.95)], CLKN, w=0.15)

# SIM_IO: SiP pin 17 -> via further left -> inner layer 3, parallel to CLK -> IO via at U4
p17 = pad_pos("U1", "17")
ION_ = net_of("U1", "17")
path([p17, V(103.6, Y(p17))], ION_, w=0.15)
via(103.6, Y(p17), ION_)
ipath([(103.6, Y(p17)), (103.6, 114.0), (108.6, 119.0), (109.45, 119.0)], ION_, w=0.15)

# SIM_RST: SiP pin 16 -> via just left of the SiP (between the VDD and SIM_IO tracks)
# -> inner layer 3, innermost of the three SIM runs -> the RST via at U4
p16 = pad_pos("U1", "16")
RSTN_ = net_of("U1", "16")
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    sys.exit("no via spot next to %s.%s" % (pad_ref, pad_num))


# LED data: SiP pin 63 runs up between the fixed DRV (62) and VDD_GPIO (65) tracks,
# drops to inner layer 3 and comes up next to U7's input
p63, u7a = pad_pos("U1", "63"), pad_pos("U7", "2")
LDN = net_of("U1", "63")
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via(pn.ToMM(int(_v[0])), pn.ToMM(int(_v[1])), LDN)
path([pn.VECTOR2I(int(_v[0]), int(_v[1])), u7a], LDN, w=0.15)

# ENABLE: pin 10 straight left to R4's ENABLE pad (between the nRESET and VDD tracks)
p10, r4e = pad_pos("U1", "10"), pad_pos("R4", "2")
path([p10, V(102.4, Y(p10)), r4e], net_of("U1", "10"), w=0.15)
# charger output: C2 (VBAT pad) joins the battery line along the left edge lane to FB1
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path([V(98.75, Y(c2v)), V(98.75, 125.0)], VB, w=0.3)
via(98.75, 125.0, VB)
bpath([(98.75, 125.0), (X(bat), 125.0), (X(bat), Y(bat))], VB, w=0.4)
# USB_DET: SiP pin 50 -> via (between the SIM holder's shield pads underneath)
# -> inner layer 3 down the right edge -> via next to the R15/R16 divider
p50, r15d = pad_pos("U1", "50"), pad_pos("R15", "2")
UDN = net_of("U1", "50")
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

hop("U6", "1", (98.75, 100.4), w=0.3)
# LED_EN: U6 pin 3 -> layer 3 -> via just above SiP pin 80 (outside the no-via zone under the SiP)
_p80 = pad_pos("U1", "80")
_code = net_of("U1", "80").GetNetCode()
for _v in spots(_p80, V(U6X, U6Y), rs=(1.0, 1.3, 1.6, 2.0)):
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        track(_p80, _v, net_of("U1", "80"), 0.15)
        break
else:
    sys.exit("no via spot for LED_EN at SiP pin 80")

# first LED's data (R18 -> D3), inside the heart: bottom side if free, else layer 3
link("R18", "2", "D3", "3")
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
